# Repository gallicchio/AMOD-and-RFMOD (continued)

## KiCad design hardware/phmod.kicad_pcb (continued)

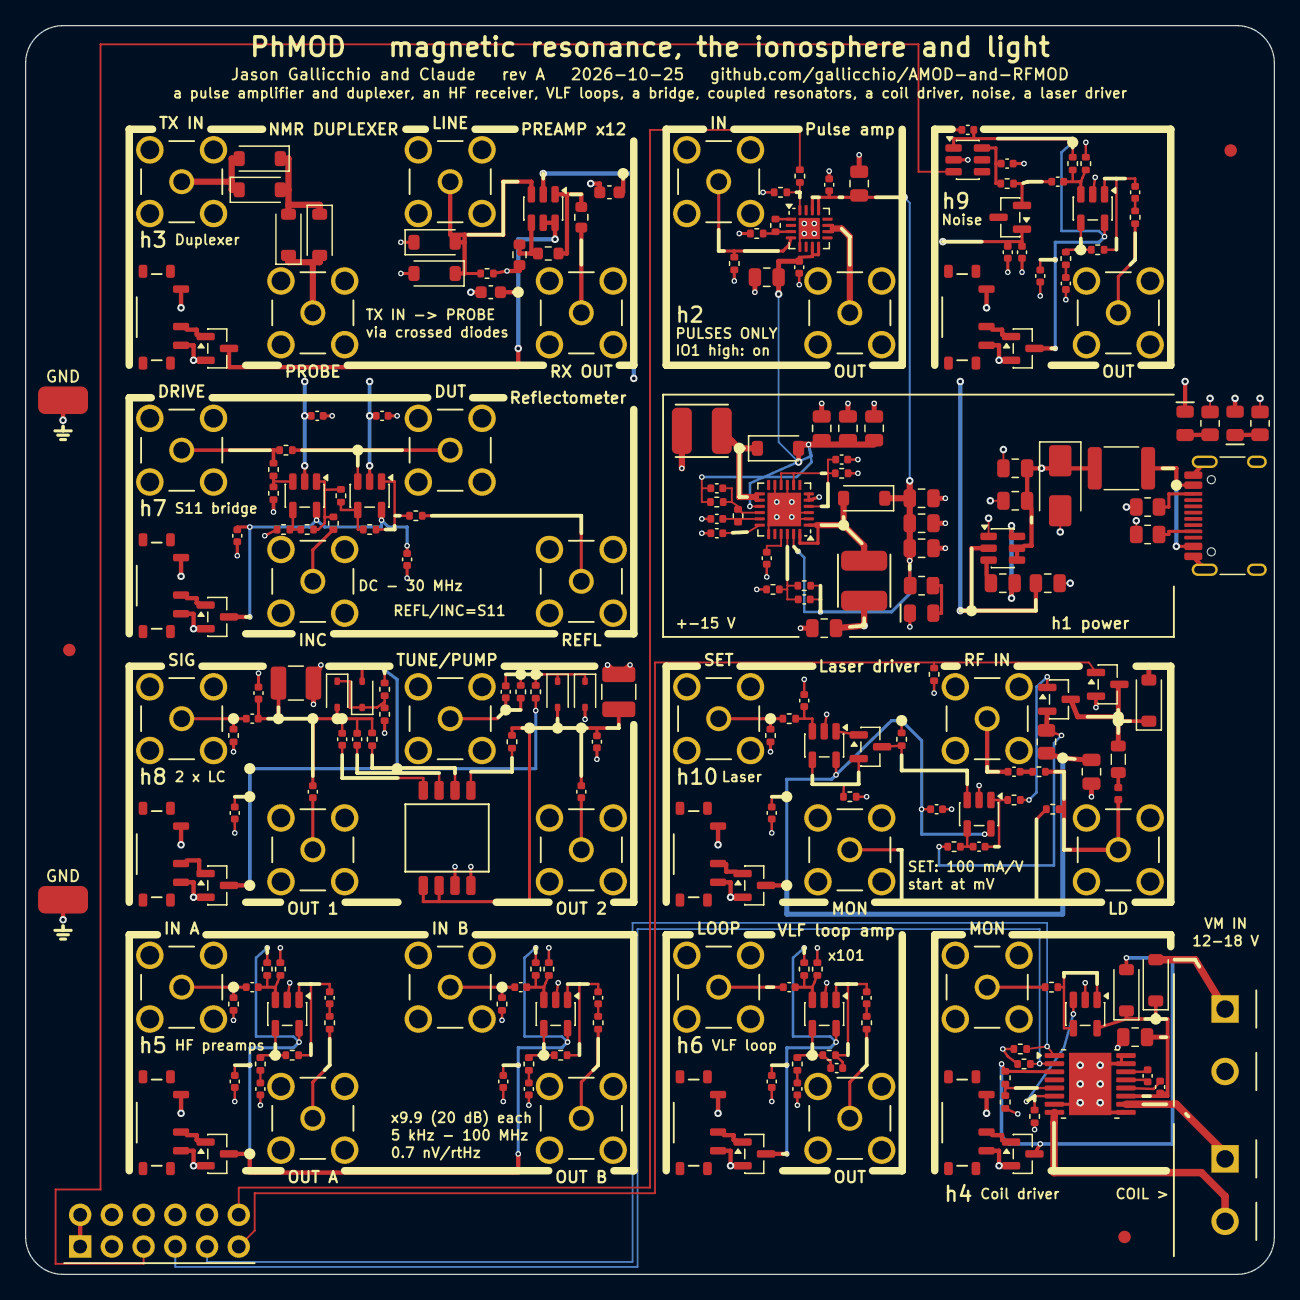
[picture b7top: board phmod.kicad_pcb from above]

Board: 4 copper layers, 100.0 x 100.0 mm, 234 parts (0 on the bottom side), 131 nets.

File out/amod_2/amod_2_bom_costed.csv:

Comment,Designator,Footprint,LCSC Part #,MPN,Qty,Unit $,Ext $,JLC
220n,C104,C_0402_1005Metric,C47129,CL05A224KA5NNNC,1,0.0083,0.008,extended
4.7n,C105,C_0402_1005Metric,C84705,CL05B472KB5NNNC,1,0.0044,0.004,extended
7.5p,C106,C_0402_1005Metric,C43514,0402CG7R5C500NT,1,0.0025,0.003,extended
4.7u,C108,C_0805_2012Metric,C1779,CL21A475KAQNNNE,1,0.0343,0.034,basic
22n,C402,C_0402_1005Metric,C337699,CL05B223KB5NNNC,1,0.0045,0.004,extended
4.7p,C802,C_0402_1005Metric,C1569,0402CG4R7C500NT,1,0.0058,0.006,extended
1p,C804,C_0402_1005Metric,C1550,0402CG1R0C500NT,1,0.0029,0.003,basic
1n,C806,C_0402_1005Metric,C1523,0402B102K500NT,1,0.0038,0.004,basic
6.8p,"C113,C807",C_0402_1005Metric,C1576,0402CG6R8C500NT,2,0.0026,0.005,extended
100n,"C301,C302",C_0603_1608Metric,C14663,CC0603KRX7R9BB104,2,0.0084,0.017,basic
10n,"C112,C1003",C_0402_1005Metric,C15195,CL05B103KB5NNNC,2,0.0039,0.008,basic
100p,"C603,C903,C1005",C_0402_1005Metric,C1546,0402CG101J500NT,3,0.0033,0.010,basic
2.2p,"C801,C803,C805,C808",C_0402_1005Metric,C1559,0402CG2R2C500NT,4,0.0037,0.015,extended
1u,"C501,C502,C503,C505,C506,C507,C601,C602,C604,C901,C905,C906,C907",C_0402_1005Metric,C14445,CL05A105KP5NNNC,13,0.0053,0.069,extended
10u,"C101,C102,C103,C109,C110,C111,C114,C115,C116,C117,C202,C204,C401,C1004",C_0805_2012Metric,C15850,CL21A106KAYNNNE,14,0.0426,0.596,basic
100n,"C107,C201,C203,C403,C504,C508,C605,C701,C702,C703,C704,C809,C902,C904,C908,C1001,C1002,C1006",C_0402_1005Metric,C1525,CL05B104KO5NNNC,18,0.0035,0.063,basic
SMAJ5.0A,D103,D_SMA,C78401,SMAJ5.0A,1,0.0537,0.054,extended
BB133,"D801,D802,D803,D804",D_SOD-323,C5334579,BB133,4,0.0604,0.242,extended
B5819W,"D101,D102,D401,D402,D1001",D_SOD-123,C64885,B5819W,5,0.0195,0.098,extended
1N4148W,"D301,D302,D303,D304,D305,D306",D_SOD-123,C81598,1N4148W,6,0.0124,0.074,basic
2A,F101,Fuse_1812_4532Metric,C210837,MF-MSMF200-2,1,0.0650,0.065,extended
USB-C,J101,USB_C_Receptacle_HRO_TYPE-C-31-M-12,C165948,TYPE-C-31-M-12,1,0.1888,0.189,extended
VM in,J402,TerminalBlock_KF301_1x02_P5.00mm,C474881,KF301-5.0-2P,1,0.1017,0.102,extended
coil,J403,TerminalBlock_KF301_1x02_P5.00mm,C474881,KF301-5.0-2P,1,0.1017,0.102,extended
Pmod,J505,PinHeader_2x06_P2.54mm_Horizontal_PZ254R-12-12P,C492434,PZ254R-12-12P,1,0.1036,0.104,extended
SMA,"J201,J202,J301,J302,J303,J304,J401,J501,J502,J503,J504,J601,J602,J701,J702,J703,J704,J801,J802,J803,J804,J901,J1001,J1002,J1003,J1004",SMA_BWSMA-KE-Z001_Vertical,C496549,BWSMA-KE-Z001,26,0.4043,10.512,extended
330n,L1001,L_0805_2012Metric,C98210,SDWL2012CR33JSTF,1,0.0851,0.085,extended
27n,L1002,L_0402_1005Metric,C882469,LQW15AN27NG80D,1,0.0902,0.090,extended
+15V,LED101,LED_0805_2012Metric_Kbar,C2296,KT-0805Y,1,0.0146,0.015,basic
-5V,LED102,LED_0805_2012Metric_Kbar,C84256,NCD0805R1,1,0.0135,0.013,basic
+5V,LED103,LED_0805_2012Metric_Kbar,C2297,KT-0805G,1,0.0164,0.016,basic
4.7u,"L101,L102",L_4x4_XRNR4030,C57269,SWPA4030S4R7MT,2,0.0603,0.121,extended
10u,"L801,L802",L_1210_3225Metric,C76835,NLV32T-100J-PF,2,0.0578,0.116,extended
MMBT3904,Q902,SOT-23,C20526,MMBT3904(RANGE:100-300),1,0.0116,0.012,basic
2N7002,Q1002,SOT-23,C8545,2N7002,1,0.0161,0.016,basic
AO3400A,Q1004,SOT-23,C20917,AO3400A,1,0.0889,0.089,basic
AO3401A,"Q301,Q401,Q501,Q601,Q701,Q801,Q901,Q1001,Q1003",SOT-23,C15127,AO3401A,9,0.0959,0.863,basic
105k,R101,R_0402_1005Metric,C25742,0402WGF1053TCE,1,0.0021,0.002,extended
1.3M,R102,R_0402_1005Metric,C423245,0402WGF1304TCE,1,0.0005,0.001,extended
88.7k,R104,R_0402_1005Metric,C25922,0402WGF8872TCE,1,0.0016,0.002,extended
1M,R105,R_0402_1005Metric,C26083,0402WGF1004TCE,1,0.0015,0.002,basic
4.7k,R106,R_0805_2012Metric,C17673,0805W8F4701T5E,1,0.0051,0.005,basic
698,R201,R_0402_1005Metric,C33359,0402WGF6980TCE,1,0.0010,0.001,extended
75,R202,R_0402_1005Metric,C25133,0402WGF750JTCE,1,0.0013,0.001,extended
4.7k,R205,R_0402_1005Metric,C25900,0402WGF4701TCE,1,0.0021,0.002,basic
1.1k,R302,R_0603_1608Metric,C22764,0603WAF1101T5E,1,0.0018,0.002,extended
49.9,R303,R_0603_1608Metric,C23185,0603WAF499JT5E,1,0.0021,0.002,basic
100R,R304,R_0603_1608Metric,C22775,0603WAF1000T5E,1,0.0023,0.002,basic
5.1k,R403,R_0402_1005Metric,C25905,0402WGF5101TCE,1,0.0023,0.002,basic
3.3k,R404,R_0402_1005Metric,C25890,0402WGF3301TCE,1,0.0036,0.004,basic
1.5k,R405,R_0402_1005Metric,C25867,0402WGF1501TCE,1,0.0029,0.003,basic
680,R901,R_0402_1005Metric,C25130,0402WGF6800TCE,1,0.0012,0.001,basic
10,R1007,R_0805_2012Metric,C17415,0805W8F100JT5E,1,0.0040,0.004,basic
47,R1008,R_0402_1005Metric,C25118,0402WGF470JTCE,1,0.0012,0.001,basic
5.1k,"R107,R108",R_0805_2012Metric,C27834,0805W8F5101T5E,2,0.0036,0.007,basic
1k,"R109,R110",R_0805_2012Metric,C17513,0805W8F1001T5E,2,0.0035,0.007,basic
2k,"R804,R807",R_0402_1005Metric,C4109,0402WGF2001TCE,2,0.0026,0.005,basic
240,"R504,R510,R904",R_0402_1005Metric,C25094,0402WGF2400TCE,3,0.0016,0.005,extended
27,"R505,R511,R905",R_0402_1005Metric,C25100,0402WGF270JTCE,3,0.0013,0.004,extended
100,"R103,R604,R1005",R_0402_1005Metric,C25076,0402WGF1000TCE,3,0.0012,0.004,basic
499,"R704,R705,R707,R708",R_0402_1005Metric,C4125,0402WGF4990TCE,4,0.0010,0.004,basic
1k,"R1002,R1003,R1004,R1006",R_0402_1005Metric,C11702,0402WGF1001TCE,4,0.0013,0.005,basic
10k,"R204,R502,R503,R508,R509,R603,R902,R903,R1009",R_0402_1005Metric,C25744,0402WGF1002TCE,9,0.0011,0.010,basic
100k,"R401,R402,R601,R602,R802,R803,R805,R806,R1010",R_0402_1005Metric,C25741,0402WGF1003TCE,9,0.0015,0.013,basic
49.9,"R203,R301,R406,R501,R506,R507,R512,R605,R701,R702,R703,R706,R709,R801,R906,R1001",R_0402_1005Metric,C25120,0402WGF499JTCE,16,0.0016,0.026,basic
DIP4,SW802,SW_DIP_SPSTx04_Slide_1.27mm_DSHP04,C40736,DSHP04TSGET,1,0.5450,0.545,extended
ON,"SW301,SW401,SW501,SW601,SW701,SW801,SW901,SW1001",SW_SPDT_Shouhan_MSK12C02,C431540,MSK12C02,8,0.0529,0.423,extended
GND,"TP9901,TP9902",TestPoint_Loop_RH-5019,C5199800,RH-5019,2,0.0966,0.193,extended
TPS65131,U101,QFN-24-1EP_4x4mm_P0.5mm_EP2.7x2.7mm,C87663,TPS65131RGER,1,2.8786,2.879,extended
LM2664,U102,SOT-23-6,C108573,LM2664M6X/NOPB,1,0.3346,0.335,extended
THS3491,U201,QFN-16-1EP_3x3mm_P0.5mm_EP1.7x1.7mm,C2058688,THS3491IRGTR,1,13.5355,13.536,extended
OPA847,U301,SOT-23-6,C160422,OPA847IDBVR,1,10.3296,10.330,extended
DRV8876,U401,HTSSOP-16-1EP_4.4x5mm_P0.65mm_EP3.4x5mm_Mask2.66x2.46mm,C575551,DRV8876PWPR,1,0.6612,0.661,extended
TPS22917,U901,SOT-23-6,C2681320,TPS22917DBVR,1,0.3653,0.365,extended
LMH6629,"U501,U502,U902",SOT-23-5,C2059678,LMH6629MFX/NOPB,3,5.4577,16.373,extended
OPA810,"U402,U601,U701,U702,U1001,U1002",SOT-23-5,C2833513,OPA810IDBVR,6,3.0996,18.598,extended
